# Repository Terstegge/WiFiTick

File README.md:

# WiFiTick
Small ESP8266-based WLAN board for the MSP432 launchpad.

Here you see WiFiTick attached to the MSP432 launchpad with an
additional EDU MKII booster pack above:

WiFiTick front and back view:

WiFiTick is a small add-on board for the
[MSP432 lauchpad](http://www.ti.com/tool/MSP-EXP432P401R) from Texas Instruments.
The MSP432 launchpad is a nice microcontroller board with a Cortex M4F processor
and a on-board debug facility. WiFiTick adds WiFi functionality to the lauchpad,
using a ESP8266, which is a cheap but very powerful WLAN-enabled microcontroller
from Espressif.

Texas Instruments have their own WiFi solution (e.g. the CC3100 booster pack).
But these boards have to be disconnected from the lauchpad when you want to 
flash a new firmware to the WiFi board. This makes it a little bit unhandy for
students.

WiFiTick has the following features:

* Low cost - ideal for WiFi enabled student projects
  (WiFi client and WiFi access point modes available)
* 4 MiB flash, so lots of space for ESP8266 programs and
  embedded file systems (SPIFFS) 
* Integrated PCB antenna
* Single 5V power supply (via USB/launchpad). There is a separate
  3.3V regulator on the board.
* No interference with other booster packs, because the additional 
  horizontal header of the MSP432 lauchpad is used
* No need to disconnect from launchpad: With a special software, the MSP432
  launchpad serves as a programming adapter (via a UART interface). This
  software features automatic baud rate control, so boot messages of the
  ESP8266 are readable.
* Easy programming of ESP8266 with Arduino IDE
* Full control of the ESP8266 from MSP432 side. The MSP432 can ...
    * Reset, Power up/down or wake up the ESP8266
    * Communicate with the ESP8266 via SPI (or any other protocol -
      there are 8 GPIOs plus the programming UART available for
      data exchange).
* Additional ADC input pad for the ESP8266
* User-controllable LED on the board (can e.g. simulate the behaviour of the
  LED on the well-known ESP-12E/F boards)

This project contains the hardware design files, which were developed
using [KiCad EDA](http://kicad.org/). The related software will be
published in a separate project.

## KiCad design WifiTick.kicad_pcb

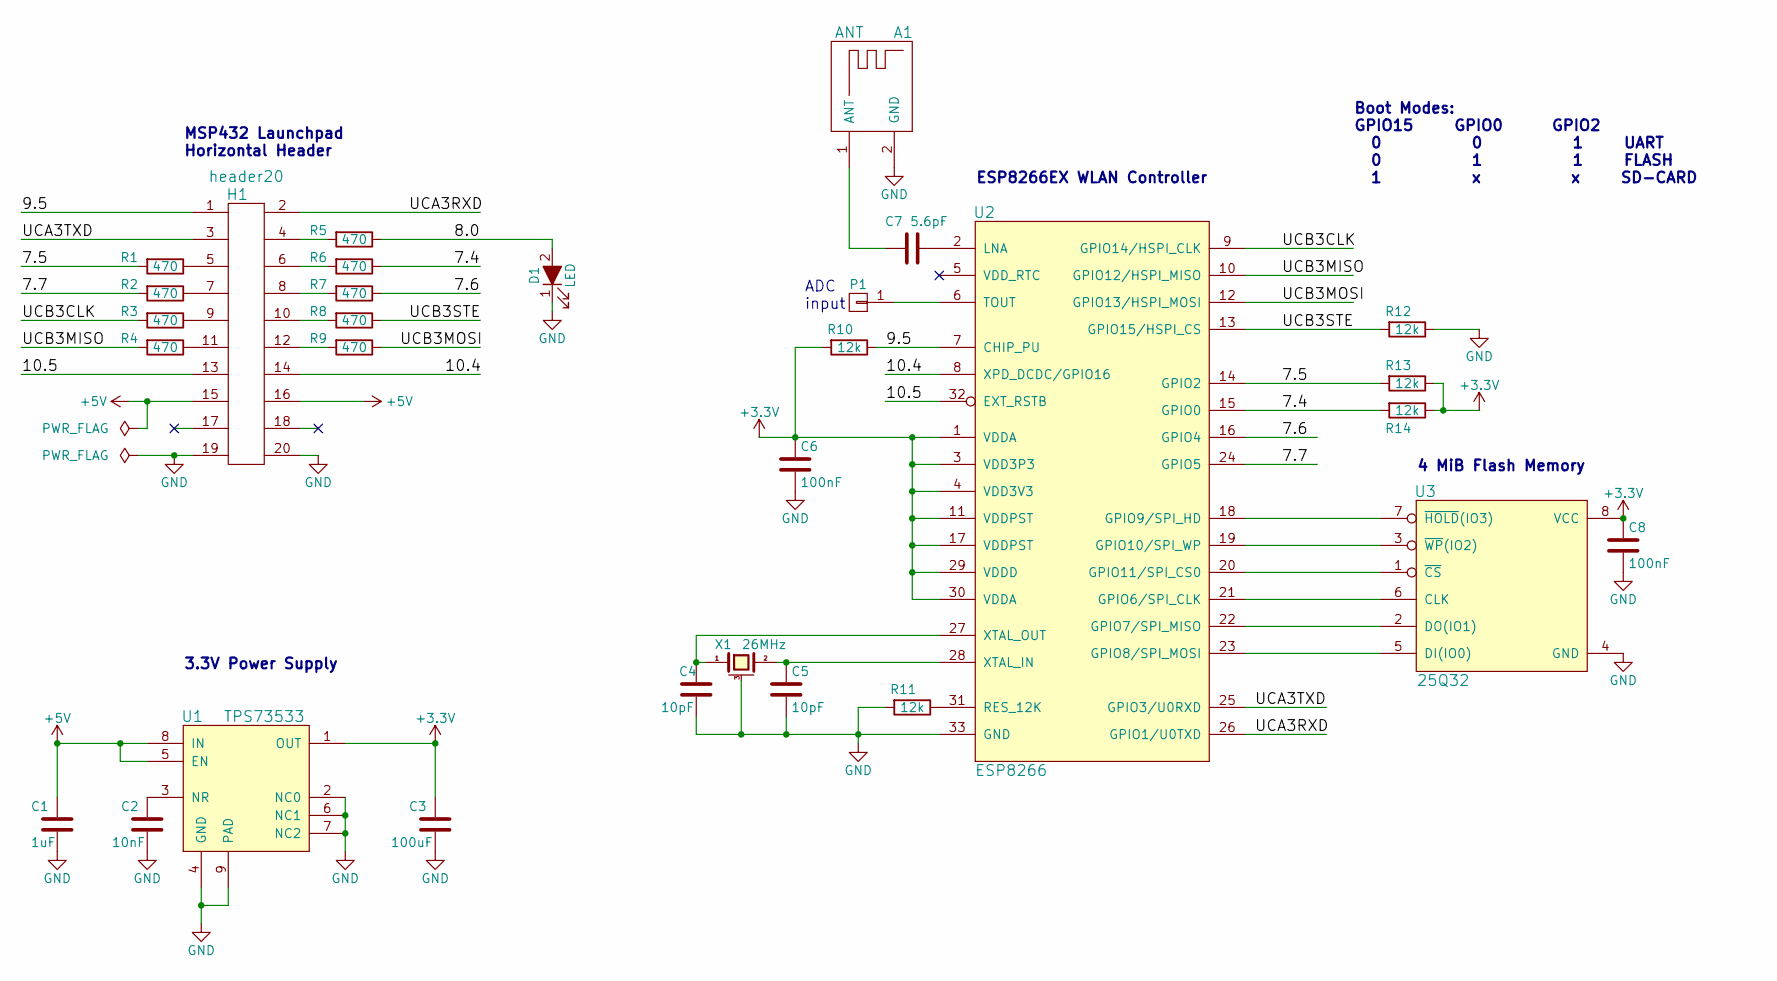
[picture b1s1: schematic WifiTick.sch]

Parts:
A1: ANT; WIFI_ANTENNA_MIRROR
C1: 1uF; C_0603
C2: 10nF; C_0603
C3: 100uF; C_1206
C4, C5: 10pF; C_0603
C6, C8: 100nF; C_0603
C7: 5.6pF; C_0603
D1: LED; LED_0603
H1: header20; Socket_Strip_Straight_2x10
P1: CONN_01X01; 1x1_Solderpad
R1, R2, R3, R4, R5, R6, R7, R8, R9: 470; R_0603
R10, R11, R12, R13, R14: 12k; R_0603
U1: TPS73533; VSON-8
U2: ESP8266; QFN-32-1EP_5x5mm_Pitch0.5mm
U3: 25Q32; SOIJ-8_5.3x5.3mm_Pitch1.27mm
X1: 26MHz; crystal_FA238-TSX3225

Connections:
+3V3: C3.1, C6.1, C8.1, R10.2, R13.1, R14.1, U1.1 (OUT), U2.1 (VDDA), U2.3 (VDD3P3), U2.4 (VDD3V3), U2.11 (VDDPST), U2.17 (VDDPST), U2.29 (VDDD), U2.30 (VDDA), U3.8 (VCC)
+5V: C1.1, H1.15, H1.16, U1.5 (EN), U1.8 (IN)
/7.4: R6.1, R14.2, U2.15 (GPIO0)
/7.5: R1.2, R13.2, U2.14 (GPIO2)
/7.6: R7.1, U2.16 (GPIO4)
/7.7: R2.2, U2.24 (GPIO5)
/8.0: D1.2 (A), R5.1
/9.5: H1.1, R10.1, U2.7 (CHIP_PU)
/10.4: H1.14, U2.8 (XPD_DCDC/GPIO16)
/10.5: H1.13, U2.32 (EXT_RSTB)
/UCA3RXD: H1.2, U2.26 (GPIO1/U0TXD)
/UCA3TXD: H1.3, U2.25 (GPIO3/U0RXD)
/UCB3CLK: R3.2, U2.9 (GPIO14/HSPI_CLK)
/UCB3MISO: R4.2, U2.10 (GPIO12/HSPI_MISO)
/UCB3MOSI: R9.1, U2.12 (GPIO13/HSPI_MOSI)
/UCB3STE: R8.1, R12.2, U2.13 (GPIO15/HSPI_CS)
GND: A1.2 (GND), C1.2, C2.2, C3.2, C4.2, C5.2, C6.2, C8.2, D1.1 (K), H1.19, H1.20, R11.2, R12.1, U1.2 (NC0), U1.4 (GND), U1.6 (NC1), U1.7 (NC2), U1.9 (PAD), U2.33 (GND), U3.4 (GND), X1.3 (case); also elsewhere on the board
unnamed: A1.1 (ANT), C7.1
unnamed: C2.1, U1.3 (NR)
unnamed: C4.1, U2.27 (XTAL_OUT), X1.1
unnamed: C5.1, U2.28 (XTAL_IN), X1.2
unnamed: C7.2, U2.2 (LNA)
unnamed: H1.4, R5.2
unnamed: H1.5, R1.1
unnamed: H1.6, R6.2
unnamed: H1.7, R2.1
unnamed: H1.8, R7.2
unnamed: H1.9, R3.1
unnamed: H1.10, R8.2
unnamed: H1.11, R4.1
unnamed: H1.12, R9.2
unnamed: P1.1, U2.6 (TOUT)
unnamed: R11.1, U2.31 (RES_12K)
unnamed: U2.18 (GPIO9/SPI_HD), U3.7 (~HOLD~(IO3))
unnamed: U2.19 (GPIO10/SPI_WP), U3.3 (~WP~(IO2))
unnamed: U2.20 (GPIO11/SPI_CS0), U3.1 (~CS)
unnamed: U2.21 (GPIO6/SPI_CLK), U3.6 (CLK)
unnamed: U2.22 (GPIO7/SPI_MISO), U3.2 (DO(IO1))
unnamed: U2.23 (GPIO8/SPI_MOSI), U3.5 (DI(IO0))

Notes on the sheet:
3.3V Power Supply
MSP432 Launchpad Horizontal Header
4 MiB Flash Memory
ESP8266EX WLAN Controller
ADC input
Boot Modes: GPIO15 GPIO0 GPIO2 0 0 1 UART 0 1 1 FLASH 1 x x SD-CARD

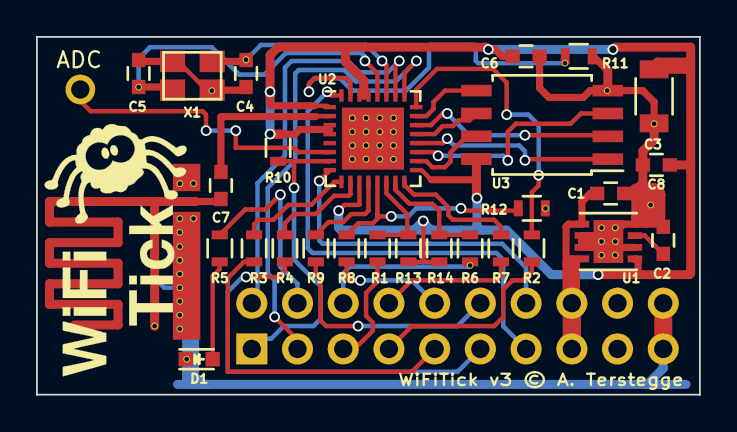
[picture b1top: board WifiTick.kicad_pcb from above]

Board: 2 copper layers, 36.8 x 19.9 mm, 31 parts (1 on the bottom side), 39 nets.

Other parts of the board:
GND: Stiching Via; StichingVia

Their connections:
GND: GND.1; also elsewhere on the board

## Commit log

2017-07-02 Added first picture.
2017-07-02 Renamed picture file.
2017-07-02 Updates to pictures
2017-07-02 First version of public files. KiCad libs might be a little bit messy...
2017-07-02 Some library cleanup. Generated Gerber files.
2020-06-18 Update due to new KiCad version.
2021-11-10 Update README.md
    https://forum.kicad.info/t/warning-avoid-all-links-to-kicad-pcb-org-use-kicad-org/31521
2021-11-12 Updated link to KiCad.

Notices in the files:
WifiTick.kicad_pcb:
WiFiTick v3 © A. Terstegge
